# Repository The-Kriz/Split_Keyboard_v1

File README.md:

Reference: [Rolio46Keyboard](https://github.com/MickiusMousius/Rolio46Keyboard)

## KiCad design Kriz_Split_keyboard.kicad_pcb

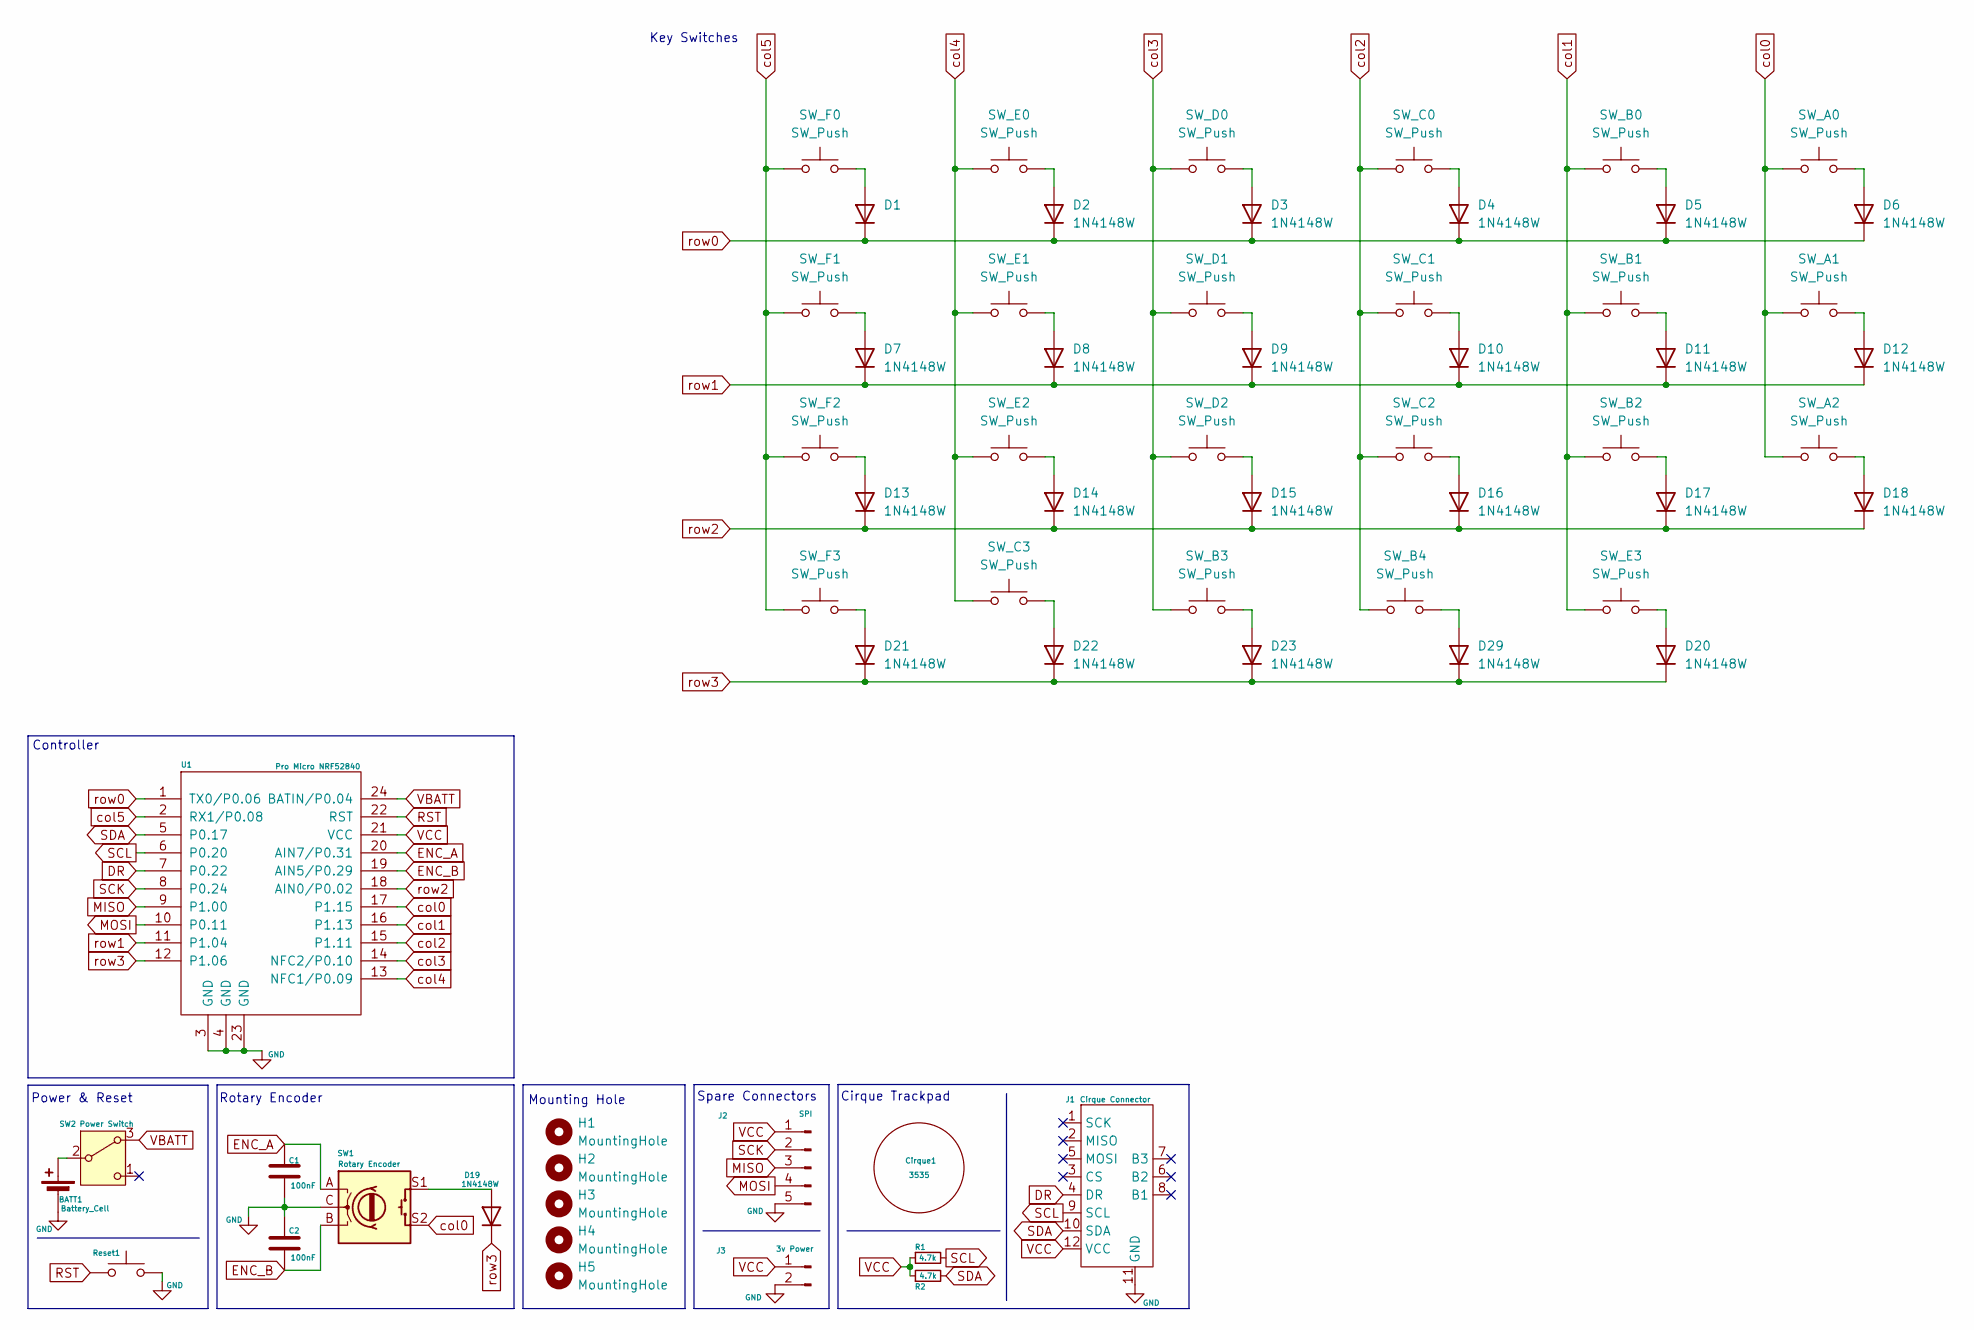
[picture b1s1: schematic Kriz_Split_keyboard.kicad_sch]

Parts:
BATT1: Battery_Cell; PinHeader_1x02_P2.00mm_Vertical
C1, C2: 100nF; C_0603_1608Metric_Pad1.08x0.95mm_HandSolder_Dualside
Cirque1: 3535; Cirque
D1, D2, D3, D4, D5, D6, D7, D8, D9, D10, D11, D12, D13, D14, D15, D16, D17, D18, D19, D20, D21, D22, D23, D29: 1N4148W; Diode_SOD123
H1, H2, H3, H4, H5: MountingHole; MountingHole_4.3mm_M4
J1: Cirque Connector; FPC-SMD_12P-P0.50_XF2M-1215-1A_Dual_Side
J2: SPI; PinHeader_1x05_P1.27mm_Vertical
J3: 3v Power; PinHeader_1x02_P2.00mm_Vertical
R1, R2: 4.7k; R_0603_1608Metric_Pad0.98x0.95mm_HandSolder_Dualside
Reset1: Reset; SW_SPST_PTS810_Dualside
SW1: Rotary Encoder; Encoder_V&H
SW2: Power Switch; SW_SPDT_PCM12_Dualside
SW_A0, SW_A1, SW_A2: SW_Push; Kailh_socket_PG1350_Dual_Side_v2
SW_B0, SW_B1, SW_B2, SW_B3, SW_B4: SW_Push; Kailh_socket_PG1350_Dual_Side_v2
SW_C0, SW_C1, SW_C2, SW_C3: SW_Push; Kailh_socket_PG1350_Dual_Side_v2
SW_D0, SW_D1, SW_D2: SW_Push; Kailh_socket_PG1350_Dual_Side_v2
SW_E0, SW_E1, SW_E2, SW_E3: SW_Push; Kailh_socket_PG1350_Dual_Side_v2
SW_F0, SW_F1, SW_F2, SW_F3: SW_Push; Kailh_socket_PG1350_Dual_Side_v2
U1: Pro Micro NRF52840; Nice Nano

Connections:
DR: J1.4 (DR), U1.7 (P0.22)
ENC_A: C1.2, SW1.A, U1.20 (AIN7/P0.31)
ENC_B: C2.2, SW1.B, U1.19 (AIN5/P0.29)
GND: BATT1.2 (-), C1.1, C2.1, J1.11 (GND), J2.5, J3.2, Reset1.2, SW1.C, U1.3 (GND), U1.4 (GND), U1.23 (GND)
MISO: J2.3, U1.9 (P1.00)
MOSI: J2.4, U1.10 (P0.11)
unnamed: BATT1.1 (+), SW2.2 (B)
unnamed: D1.2 (A), SW_F0.2
unnamed: D2.2 (A), SW_E0.2
unnamed: D3.2 (A), SW_D0.2
unnamed: D4.2 (A), SW_C0.2
unnamed: D5.2 (A), SW_B0.2
unnamed: D6.2 (A), SW_A0.2
unnamed: D7.2 (A), SW_F1.2
unnamed: D8.2 (A), SW_E1.2
unnamed: D9.2 (A), SW_D1.2
unnamed: D10.2 (A), SW_C1.2
unnamed: D11.2 (A), SW_B1.2
unnamed: D12.2 (A), SW_A1.2
unnamed: D13.2 (A), SW_F2.2
unnamed: D14.2 (A), SW_E2.2
unnamed: D15.2 (A), SW_D2.2
unnamed: D16.2 (A), SW_C2.2
unnamed: D17.2 (A), SW_B2.2
unnamed: D18.2 (A), SW_A2.2
unnamed: D19.2 (A), SW1.S1
unnamed: D20.2 (A), SW_E3.2
unnamed: D21.2 (A), SW_F3.2
unnamed: D22.2 (A), SW_C3.2
unnamed: D23.2 (A), SW_B3.2
unnamed: D29.2 (A), SW_B4.2
RST: Reset1.1, U1.22 (RST)
SCK: J2.2, U1.8 (P0.24)
SCL: J1.9 (SCL), R1.2, U1.6 (P0.20)
SDA: J1.10 (SDA), R2.2, U1.5 (P0.17)
VBATT: SW2.3 (A), U1.24 (BATIN/P0.04)
VCC: J1.12 (VCC), J2.1, J3.1, R1.1, R2.1, U1.21 (VCC)
col0: SW1.S2, SW_A0.1, SW_A1.1, SW_A2.1, U1.17 (P1.15)
col1: SW_B0.1, SW_B1.1, SW_B2.1, SW_E3.1, U1.16 (P1.13)
col2: SW_B4.1, SW_C0.1, SW_C1.1, SW_C2.1, U1.15 (P1.11)
col3: SW_B3.1, SW_D0.1, SW_D1.1, SW_D2.1, U1.14 (NFC2/P0.10)
col4: SW_C3.1, SW_E0.1, SW_E1.1, SW_E2.1, U1.13 (NFC1/P0.09)
col5: SW_F0.1, SW_F1.1, SW_F2.1, SW_F3.1, U1.2 (RX1/P0.08)
row0: D1.1 (K), D2.1 (K), D3.1 (K), D4.1 (K), D5.1 (K), D6.1 (K), U1.1 (TX0/P0.06)
row1: D7.1 (K), D8.1 (K), D9.1 (K), D10.1 (K), D11.1 (K), D12.1 (K), U1.11 (P1.04)
row2: D13.1 (K), D14.1 (K), D15.1 (K), D16.1 (K), D17.1 (K), D18.1 (K), U1.18 (AIN0/P0.02)
row3: D19.1 (K), D20.1 (K), D21.1 (K), D22.1 (K), D23.1 (K), D29.1 (K), U1.12 (P1.06)

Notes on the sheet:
Rotary Encoder
Power & Reset
Key Switches
Controller
Spare Connectors
Mounting Hole
Cirque Trackpad

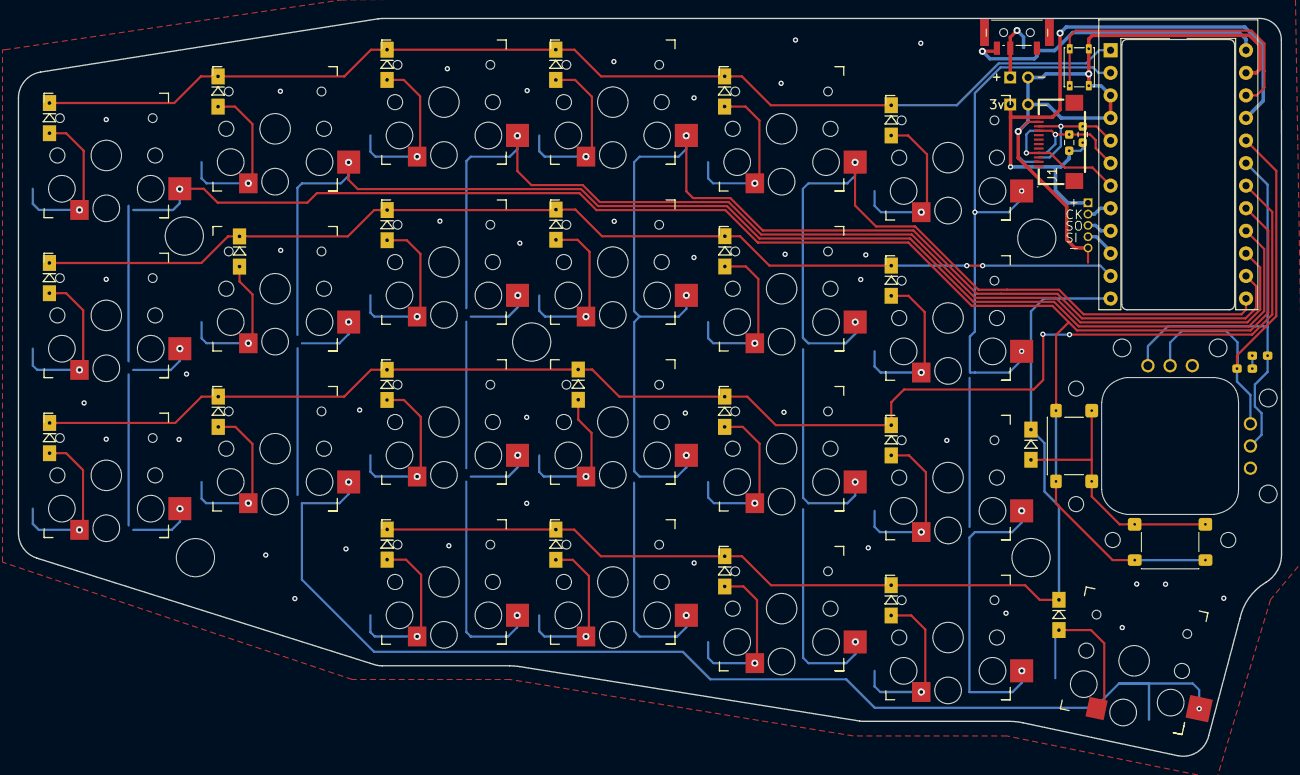
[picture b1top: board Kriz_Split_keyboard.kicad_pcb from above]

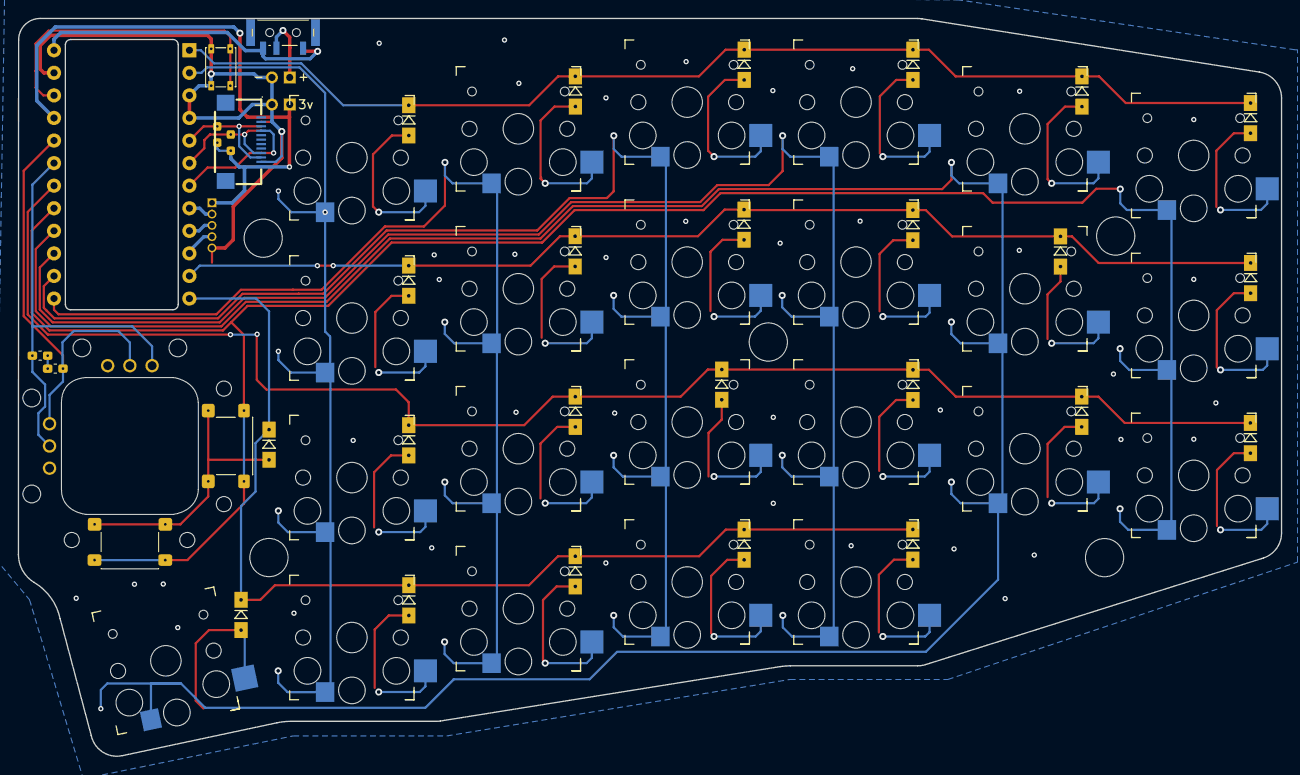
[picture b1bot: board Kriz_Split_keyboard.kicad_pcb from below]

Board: 2 copper layers, 142.1 x 83.0 mm, 65 parts (26 on the bottom side), 47 nets.

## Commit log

2026-03-10 Test Encoder
2026-03-10 Add images to README
    Added images to the README for better visualization.
2026-05-22 Restore and add images to README.md
